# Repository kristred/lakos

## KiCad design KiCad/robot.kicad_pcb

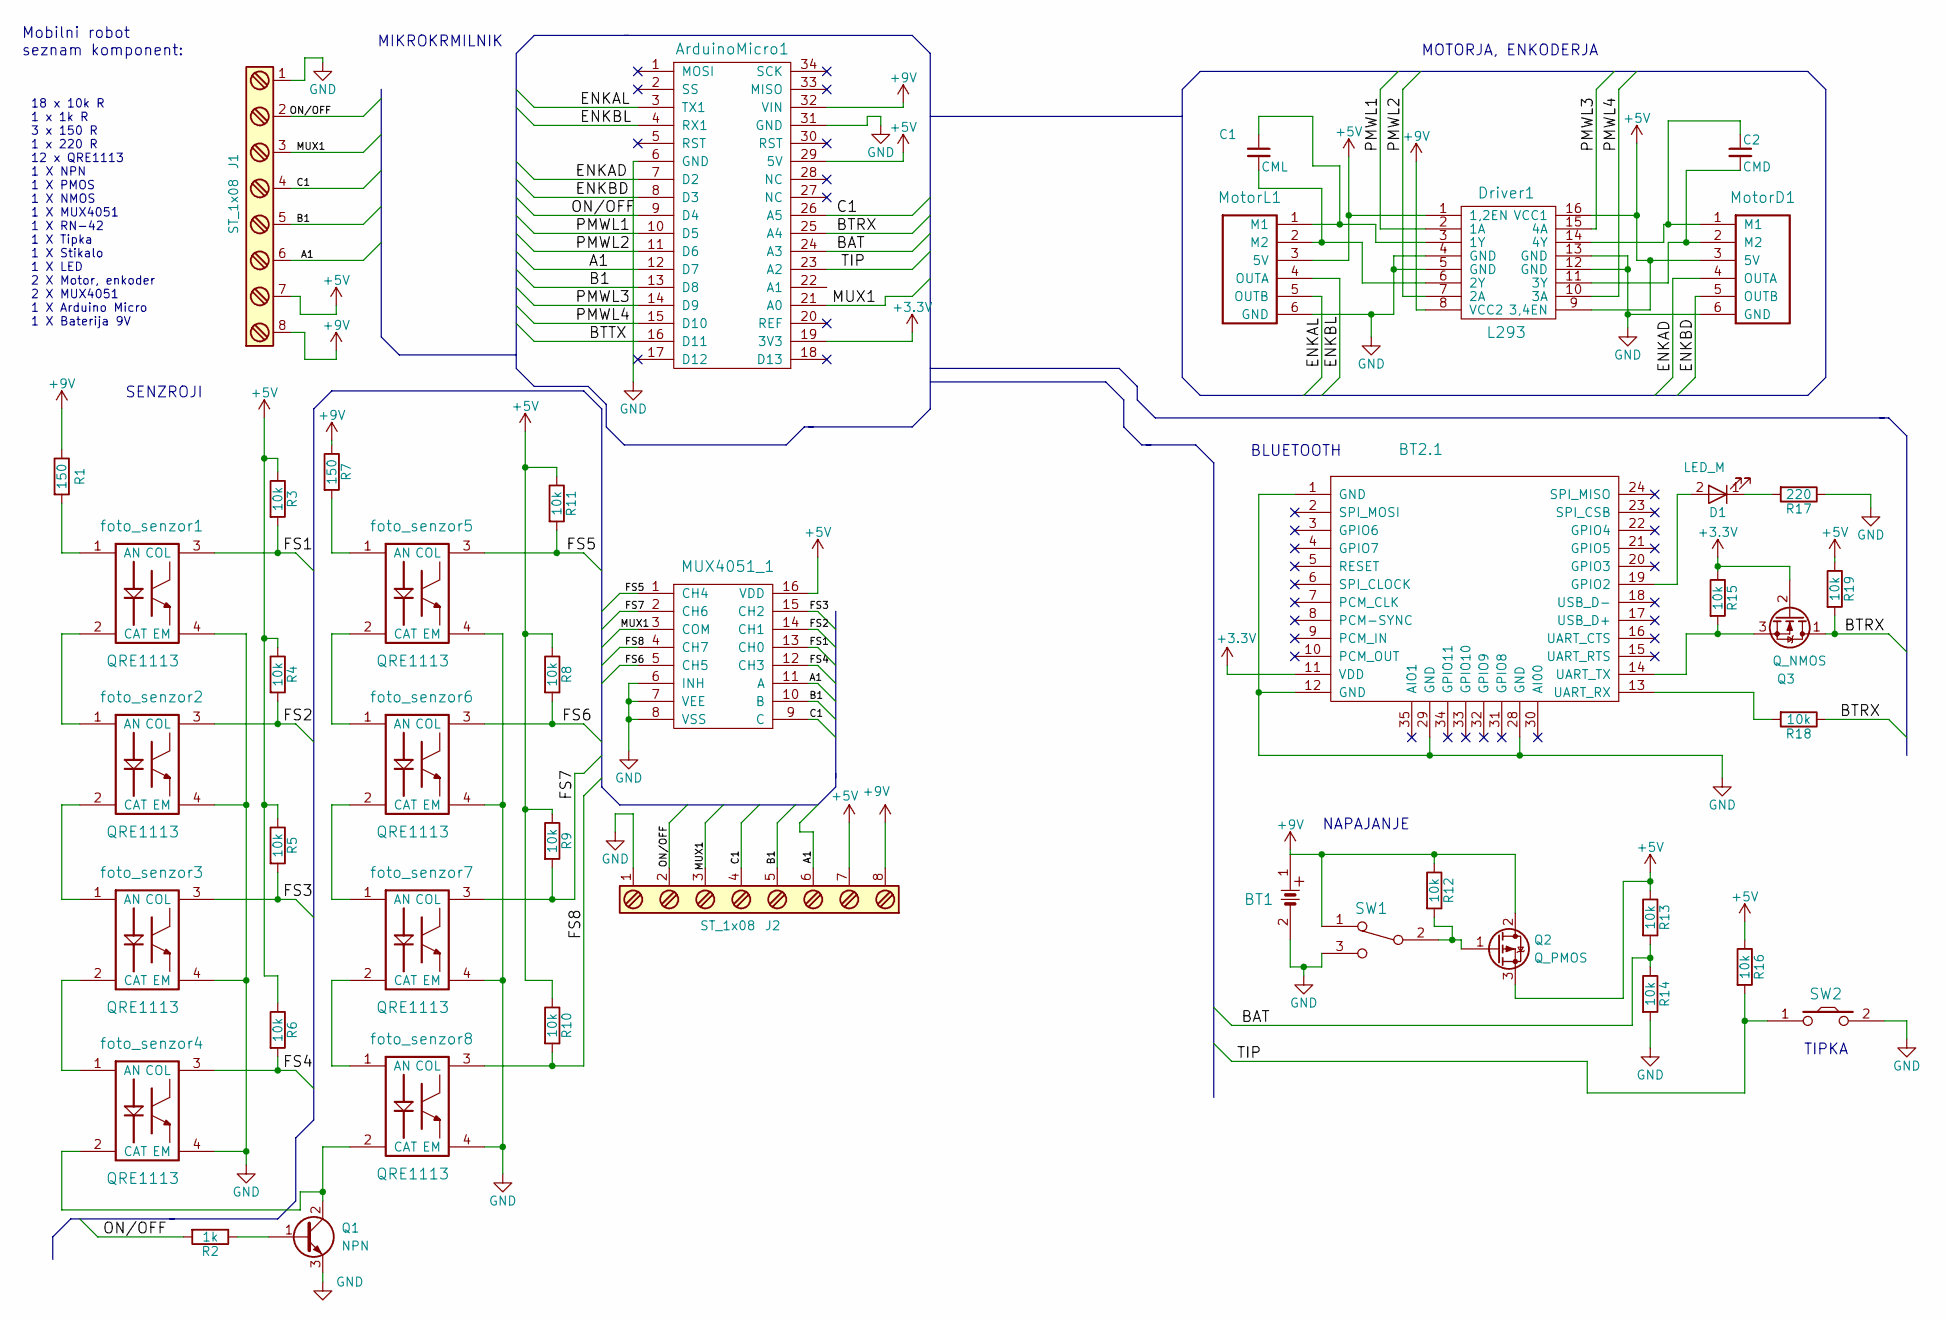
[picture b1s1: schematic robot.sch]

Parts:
ArduinoMicro1: Arduino_Micro; ArduinoMicro
BT1: BATTERY; Battery
BT2.1: RN-42; RN42
C1: CML; C_Rect_L4_W2.5_P2.5
C2: CMD; C_Rect_L4_W2.5_P2.5
D1: LED_M; D_0603
Driver1: L293; DIP-16_W7.62mm_LongPads
J1, J2: ST_1x08; ST_1x8
MUX4051_1: CD4051
MotorD1: MicrGearMotor2; Motor
MotorL1: MicroGearMotor; Motor
Q1: NPN; TO-92_Inline_Narrow_Oval
Q2: Q_PMOS; TO-220_Neutral123_Vertical
Q3: Q_NMOS; SOT-23
R1, R7: 150; R_0805_HandSoldering
R2: 1k; R_0805_HandSoldering
R3, R4, R5, R6, R8, R9, R10, R11, R12, R13, R14, R15, R16, R18, R19: 10k; R_0805_HandSoldering
R17: 220; R_0805_HandSoldering
SW1: SWITCH_INV; Switch
SW2: switch_push; SW_PUSH_SMALL
foto_senzor1, foto_senzor2, foto_senzor3, foto_senzor4, foto_senzor5, foto_senzor6, foto_senzor7, foto_senzor8: QRE1113

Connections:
+3V3: ArduinoMicro1.19 (3V3), BT2.1.11 (VDD), Q3.2 (G), R15.1
+5V: ArduinoMicro1.29 (5V), Driver1.1 (1,2EN), Driver1.9 (3,4EN), Driver1.16 (VCC1), J1.7, J2.7, MUX4051_1.16 (VDD), MotorD1.3 (5V), MotorL1.3 (5V), Q2.3 (S), R3.1, R4.1, R5.1, R6.1, R8.1, R9.1, R10.1, R11.1, R13.1, R16.1, R19.1
+9V: ArduinoMicro1.32 (VIN), BT1.1, Driver1.8 (VCC2), J1.8, J2.8, Q2.2 (D), R1.1, R7.1, R12.1, SW1.1
/A1: ArduinoMicro1.12 (D7), J1.6, J2.6, MUX4051_1.11 (A)
/B1: ArduinoMicro1.13 (D8), J1.5, J2.5, MUX4051_1.10 (B)
/BAT: ArduinoMicro1.24 (A3), R13.2, R14.1
/BTRX: ArduinoMicro1.25 (A4), Q3.1 (D), R18.1, R19.2
/BTTX: ArduinoMicro1.16 (D11)
/C1: ArduinoMicro1.26 (A5), J1.4, J2.4, MUX4051_1.9 (C)
/ENKAD: ArduinoMicro1.7 (D2), MotorD1.4 (OUTA)
/ENKAL: ArduinoMicro1.3 (TX1), MotorL1.5 (OUTB)
/ENKBD: ArduinoMicro1.8 (D3), MotorD1.5 (OUTB)
/ENKBL: ArduinoMicro1.4 (RX1), MotorL1.4 (OUTA)
/FS1: MUX4051_1.13 (CH0), R3.2, foto_senzor1.3 (COL)
/FS2: MUX4051_1.14 (CH1), R4.2, foto_senzor2.3 (COL)
/FS3: MUX4051_1.15 (CH2), R5.2, foto_senzor3.3 (COL)
/FS4: MUX4051_1.12 (CH3), R6.2, foto_senzor4.3 (COL)
/FS5: MUX4051_1.1 (CH4), R11.2, foto_senzor5.3 (COL)
/FS6: MUX4051_1.5 (CH5), R8.2, foto_senzor6.3 (COL)
/FS7: MUX4051_1.2 (CH6), R9.2, foto_senzor7.3 (COL)
/FS8: MUX4051_1.4 (CH7), R10.2, foto_senzor8.3 (COL)
/MUX1: ArduinoMicro1.21 (A0), J1.3, J2.3, MUX4051_1.3 (COM)
/ON/OFF: ArduinoMicro1.9 (D4), J1.2, J2.2, R2.2
/PMWL1: ArduinoMicro1.10 (D5), Driver1.2 (1A)
/PMWL2: ArduinoMicro1.11 (D6), Driver1.7 (2A)
/PMWL3: ArduinoMicro1.14 (D9), Driver1.15 (4A)
/PMWL4: ArduinoMicro1.15 (D10), Driver1.10 (3A)
/TIP: ArduinoMicro1.23 (A2), R16.2, SW2.1
GND: ArduinoMicro1.6 (GND), ArduinoMicro1.31 (GND), BT1.2, BT2.1.1 (GND), BT2.1.12 (GND), BT2.1.28 (GND), BT2.1.29 (GND), Driver1.4 (GND), Driver1.5 (GND), Driver1.12 (GND), Driver1.13 (GND), J1.1, J2.1, MUX4051_1.6 (INH), MUX4051_1.7 (VEE), MUX4051_1.8 (VSS), MotorD1.6 (GND), MotorL1.6 (GND), Q1.3 (E), R14.2, R17.1, SW1.3, SW2.2, foto_senzor1.4 (EM), foto_senzor2.4 (EM), foto_senzor3.4 (EM), foto_senzor4.4 (EM), foto_senzor5.4 (EM), foto_senzor6.4 (EM), foto_senzor7.4 (EM), foto_senzor8.4 (EM)
unnamed: BT2.1.13 (UART_RX), R18.2
unnamed: BT2.1.14 (UART_TX), Q3.3 (S), R15.2
unnamed: BT2.1.19 (GPIO2), D1.2 (A)
unnamed: C1.1, Driver1.3 (1Y), MotorL1.1 (M1)
unnamed: C1.2, Driver1.6 (2Y), MotorL1.2 (M2)
unnamed: C2.1, Driver1.14 (4Y), MotorD1.1 (M1)
unnamed: C2.2, Driver1.11 (3Y), MotorD1.2 (M2)
unnamed: D1.1 (K), R17.2
unnamed: Q1.1 (B), R2.1
unnamed: Q1.2 (C), foto_senzor4.2 (CAT), foto_senzor8.2 (CAT)
unnamed: Q2.1 (G), R12.2, SW1.2
unnamed: R1.2, foto_senzor1.1 (AN)
unnamed: R7.2, foto_senzor5.1 (AN)
unnamed: foto_senzor1.2 (CAT), foto_senzor2.1 (AN)
unnamed: foto_senzor2.2 (CAT), foto_senzor3.1 (AN)
unnamed: foto_senzor3.2 (CAT), foto_senzor4.1 (AN)
unnamed: foto_senzor5.2 (CAT), foto_senzor6.1 (AN)
unnamed: foto_senzor6.2 (CAT), foto_senzor7.1 (AN)
unnamed: foto_senzor7.2 (CAT), foto_senzor8.1 (AN)

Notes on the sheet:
Mobilni robot seznam komponent:
SENZROJI
NAPAJANJE
BLUETOOTH
TIPKA
MOTORJA, ENKODERJA
MIKROKRMILNIK
18 x 10k R 1 x 1k R 3 x 150 R 1 x 220 R 12 x QRE1113 1 X NPN 1 X PMOS 1 X NMOS 1 X MUX4051 1 X RN-42 1 X Tipka 1 X Stikalo 1 X LED 2 X Motor, enkoder 2 X MUX4051 1 X Arduino Micro 1 X Baterija 9V

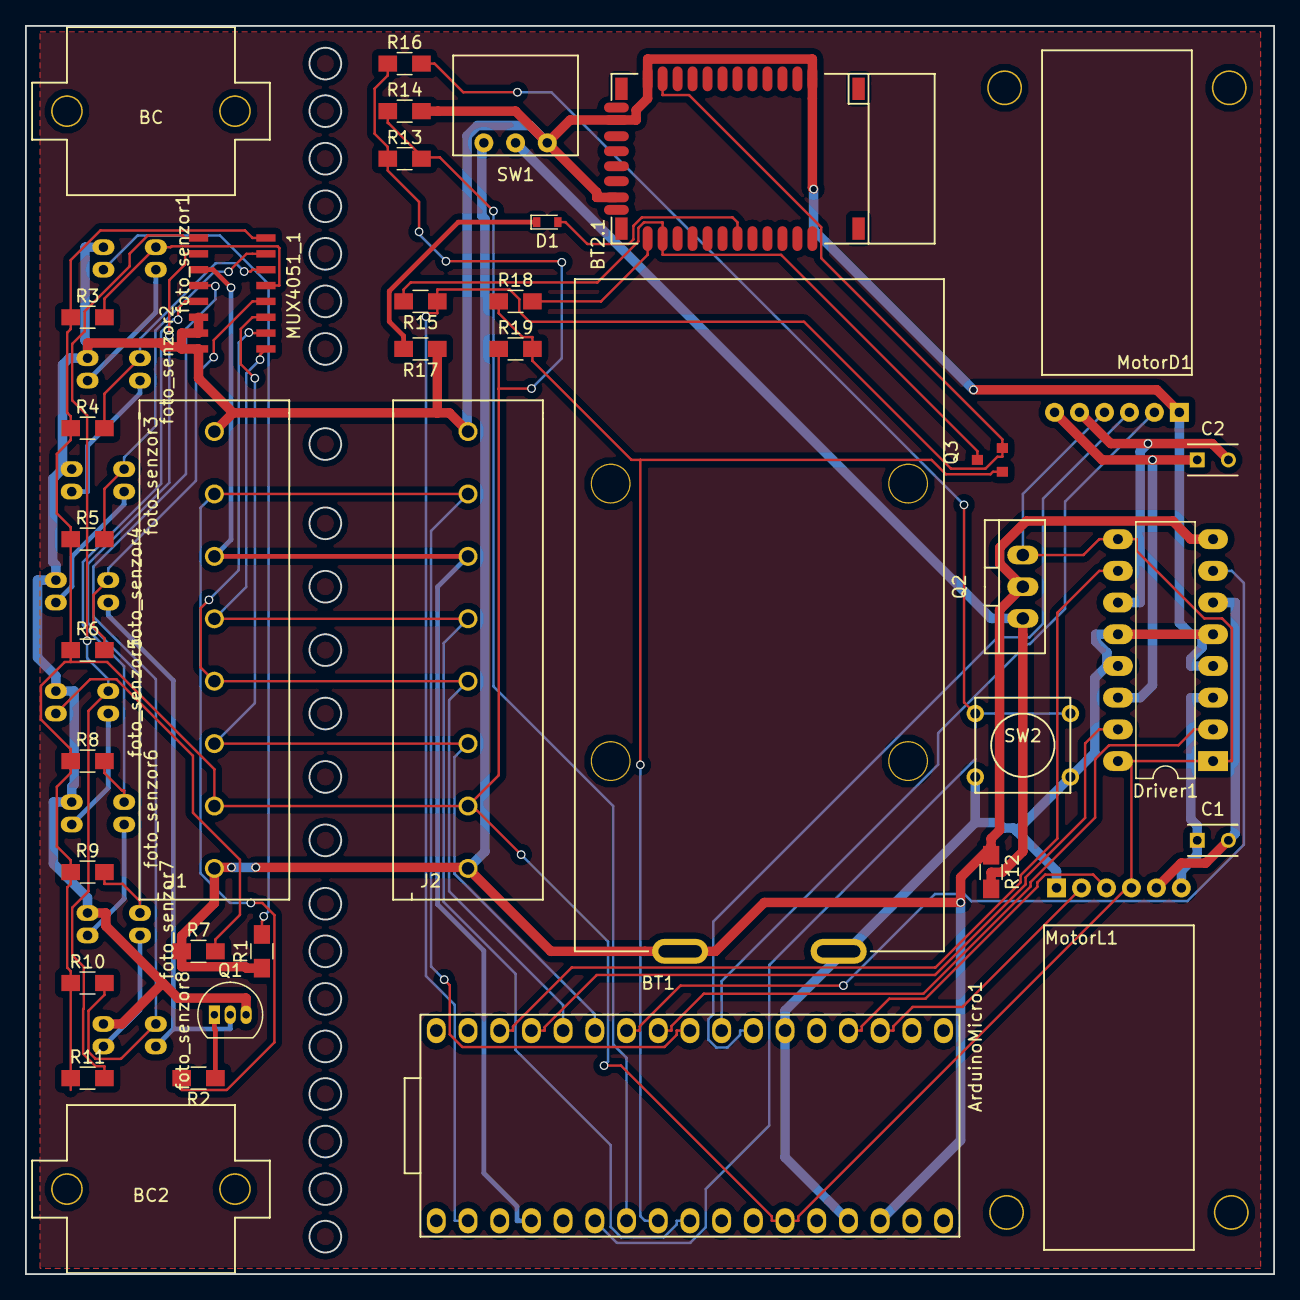
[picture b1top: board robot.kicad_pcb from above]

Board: 2 copper layers, 100.0 x 100.0 mm, 46 parts (0 on the bottom side), 47 nets.

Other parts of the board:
BC, BC2: ball_caster

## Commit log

2017-02-24 proba
2017-03-06 izbira komponent,komponente v knjižnico robot
2017-03-12 dodana shema
2017-03-17 popravljeni pini
2017-03-27 Narejen PCB
